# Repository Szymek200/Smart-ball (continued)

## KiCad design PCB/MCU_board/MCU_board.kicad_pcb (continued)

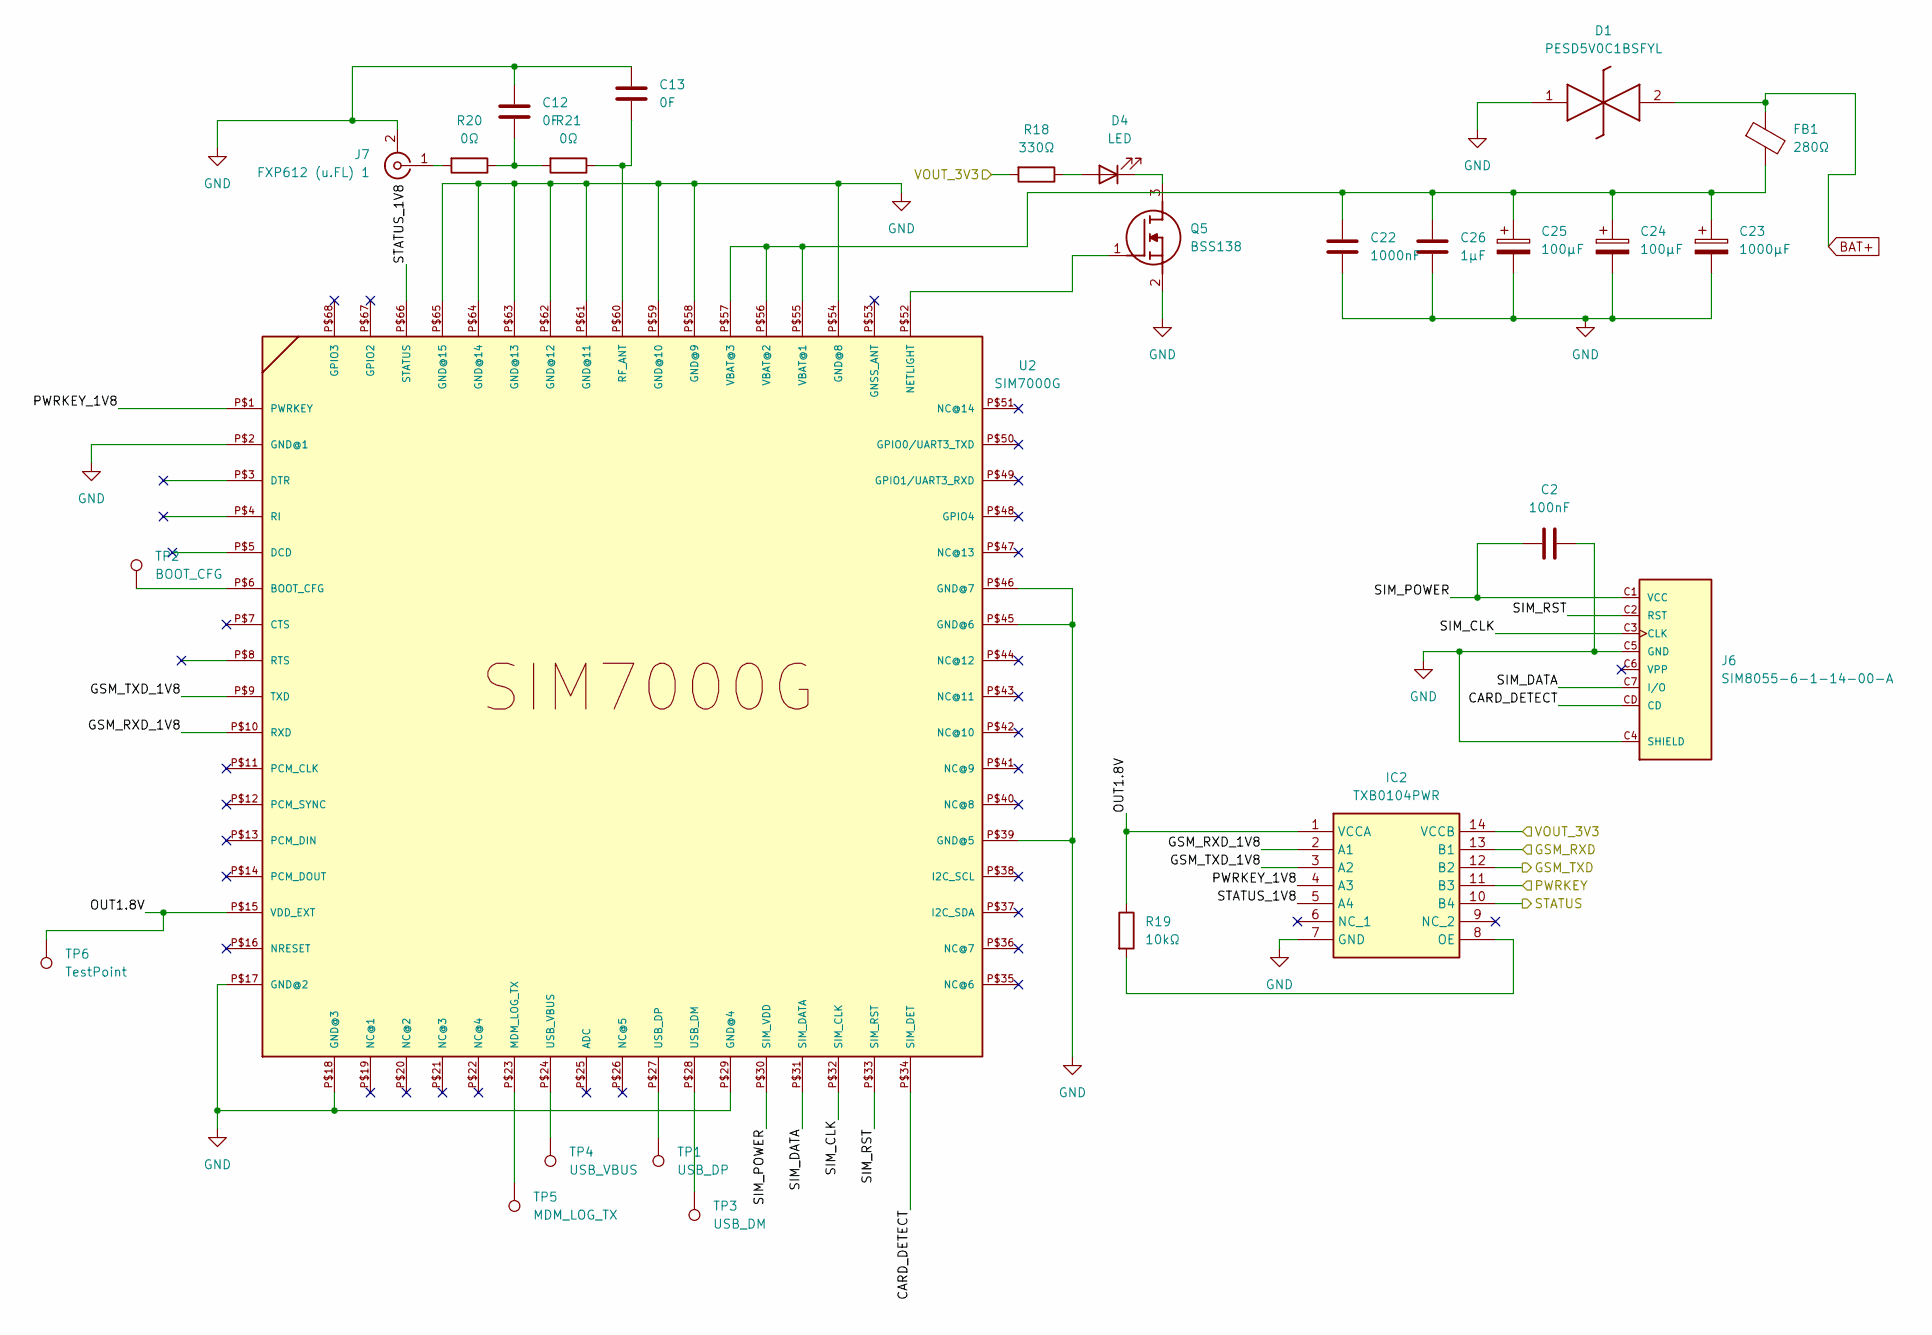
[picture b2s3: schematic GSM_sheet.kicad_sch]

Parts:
C2: 100nF; CP_Elec_6.3x5.4
C12, C13: 0F; CP_Elec_6.3x5.4
C22: 1000nF; CP_Elec_6.3x5.4
C23: 1000µF; CP_EIA-3216-18_Kemet-A
C24, C25: 100µF; CP_EIA-3216-18_Kemet-A
C26: 1µF; CP_Elec_6.3x5.4
D1: PESD5V0C1BSFYL; PMEG3005AESFYL; Mouser Part Number 771-PESD5V0C1BSFYL
D4: LED; LED_0603_1608Metric
FB1: 280Ω; L_0805_2012Metric_Pad1.05x1.20mm_HandSolder
IC2: TXB0104PWR; SOP65P640X120-14N; Mouser Part Number 595-TXB0104PWR
J6: SIM8055-6-1-14-00-A; GCT_SIM8055-6-1-14-00-A; PARTREV A1
J7: FXP612 (u.FL) 1; U.FL_Molex_MCRF_73412-0110_Vertical
Q5: BSS138; SOT95P240X120-3N; Mouser Part Number 512-BSS138
R18: 330Ω; R_0603_1608Metric
R19: 10kΩ; R_0603_1608Metric
R20, R21: 0Ω; R_0603_1608Metric
TP1: USB_DP; TestPoint_THTPad_D2.0mm_Drill1.0mm
TP2: BOOT_CFG; TestPoint_THTPad_D2.0mm_Drill1.0mm
TP3: USB_DM; TestPoint_THTPad_D2.0mm_Drill1.0mm
TP4: USB_VBUS; TestPoint_THTPad_D2.0mm_Drill1.0mm
TP5: MDM_LOG_TX; TestPoint_THTPad_D2.0mm_Drill1.0mm
TP6: TestPoint; TestPoint_THTPad_D2.0mm_Drill1.0mm
U2: SIM7000G

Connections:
/+3V3: IC2.14 (VCCB), R18.2; also elsewhere on the board
/GSM_RXT: IC2.13 (B1); also elsewhere on the board
/GSM_TXD: IC2.12 (B2); also elsewhere on the board
/PWRKEY: IC2.11 (B3); also elsewhere on the board
/STATUS: IC2.10 (B4); also elsewhere on the board
/Stationary/GSM_sheet/CARD_DETECT: J6.CD, U2.P$34 (SIM_DET)
/Stationary/GSM_sheet/GSM_RXD_1V8: IC2.2 (A1), U2.P$10 (RXD)
/Stationary/GSM_sheet/GSM_TXD_1V8: IC2.3 (A2), U2.P$9 (TXD)
/Stationary/GSM_sheet/OUT1.8V: IC2.1 (VCCA), R19.1, TP6.1 (1_1), U2.P$15 (VDD_EXT)
/Stationary/GSM_sheet/PWRKEY_1V8: IC2.4 (A3), U2.P$1 (PWRKEY)
/Stationary/GSM_sheet/SIM_CLK: J6.C3 (CLK), U2.P$32 (SIM_CLK)
/Stationary/GSM_sheet/SIM_DATA: J6.C7 (I/O), U2.P$31 (SIM_DATA)
/Stationary/GSM_sheet/SIM_POWER: C2.2, J6.C1 (VCC), U2.P$30 (SIM_VDD)
/Stationary/GSM_sheet/SIM_RST: J6.C2 (RST), U2.P$33 (SIM_RST)
/Stationary/GSM_sheet/STATUS_1V8: IC2.5 (A4), U2.P$66 (STATUS)
BAT+: D1.2 (K2), FB1.1; also elsewhere on the board
GND: C2.1, C12.1, C13.1, C22.2, C23.2, C24.2, C25.2, C26.2, D1.1 (K1), IC2.7 (GND), J6.C4 (SHIELD), J6.C5 (GND), J6.C8 (SHIELD), J7.2 (Ext), Q5.2 (S), U2.P$2 (GND@1), U2.P$17 (GND@2), U2.P$18 (GND@3), U2.P$29 (GND@4), U2.P$39 (GND@5), U2.P$45 (GND@6), U2.P$46 (GND@7), U2.P$54 (GND@8), U2.P$58 (GND@9), U2.P$59 (GND@10), U2.P$61 (GND@11), U2.P$62 (GND@12), U2.P$63 (GND@13), U2.P$64 (GND@14), U2.P$65 (GND@15); also elsewhere on the board
unnamed: C12.2, R20.1, R21.2
unnamed: D4.2 (A), R18.1
unnamed: D4.1 (K), Q5.3 (D)
unnamed: IC2.8 (OE), R19.2
unnamed: J7.1 (In), R20.2
unnamed: Q5.1 (G), U2.P$52 (NETLIGHT)
unnamed: TP2.1 (1_1), U2.P$6 (BOOT_CFG)
unnamed: TP5.1 (1_1), U2.P$23 (MDM_LOG_TX)
unnamed: C13.2, R21.1, U2.P$60 (RF_ANT)
unnamed: TP3.1 (1_1), U2.P$28 (USB_DM)
unnamed: TP1.1 (1_1), U2.P$27 (USB_DP)
unnamed: TP4.1 (1_1), U2.P$24 (USB_VBUS)
unnamed: C22.1, C23.1, C24.1, C25.1, C26.1, FB1.2, U2.P$55 (VBAT@1), U2.P$56 (VBAT@2), U2.P$57 (VBAT@3)

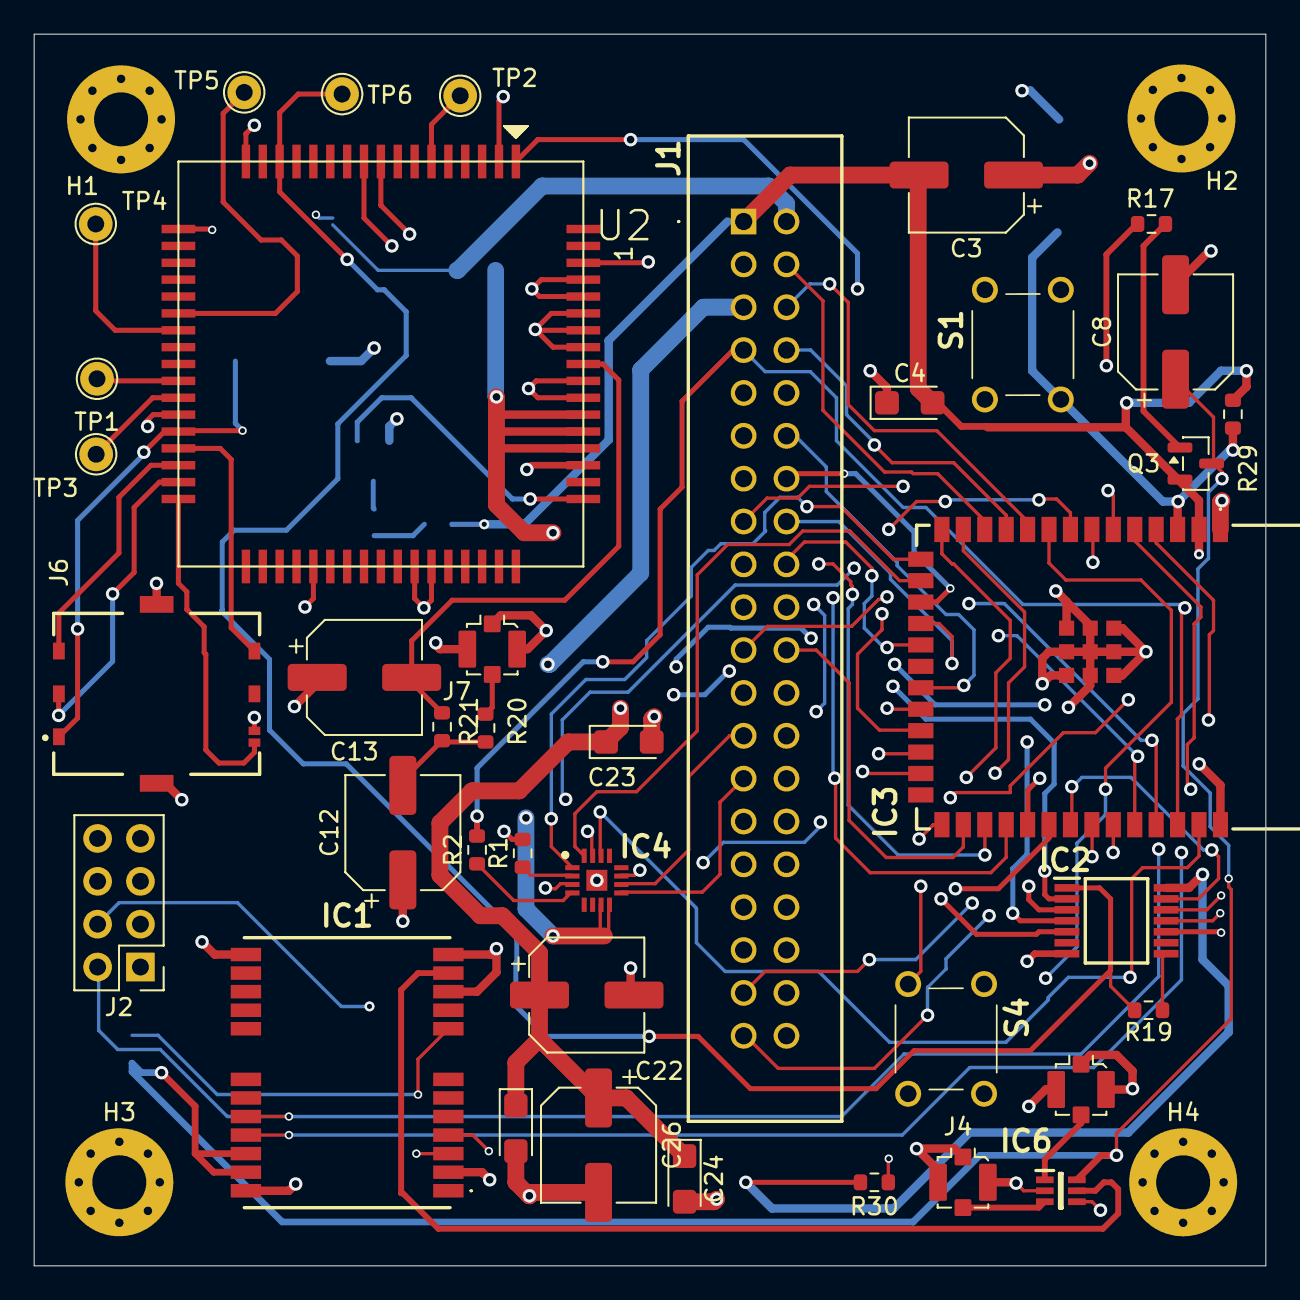
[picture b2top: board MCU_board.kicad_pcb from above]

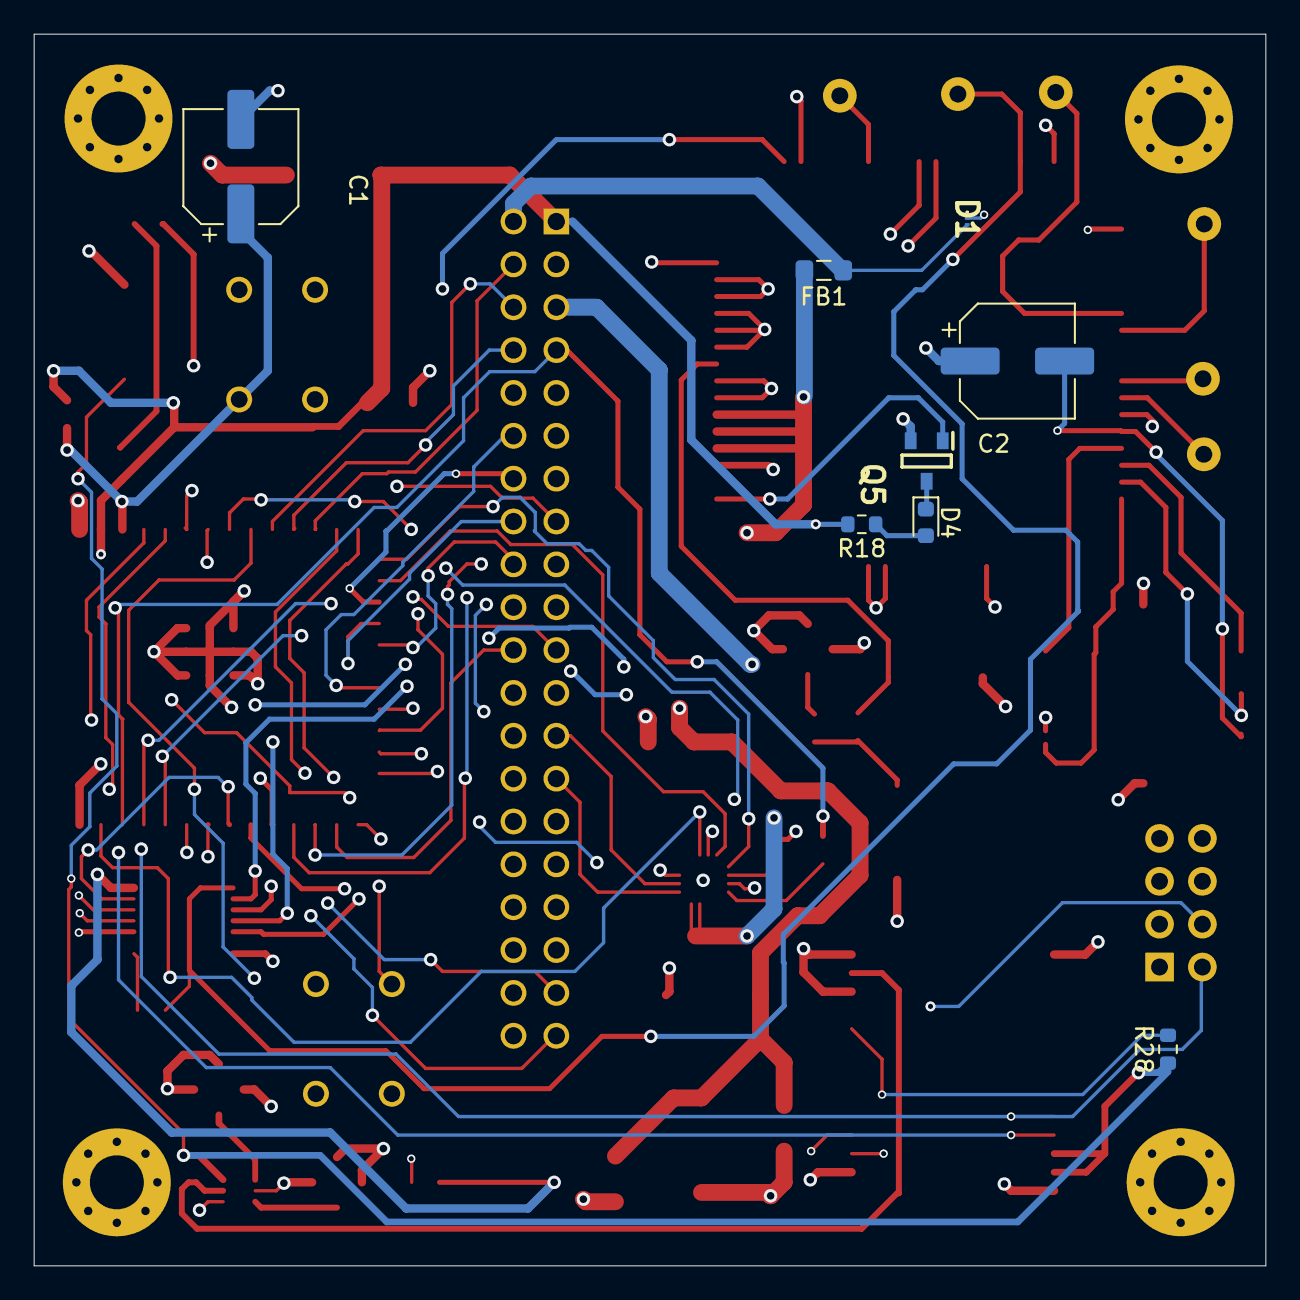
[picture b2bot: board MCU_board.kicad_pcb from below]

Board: 4 copper layers, 73.0 x 73.0 mm, 51 parts (8 on the bottom side), 72 nets.

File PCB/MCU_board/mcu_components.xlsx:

Designator | Footprint | Quantity | Value | LCSC Part #
C1, C26 | C_Disc_D5.0mm_W2.5mm_P2.50mm | 2 | 1μF
C12, C13 | C_Disc_D5.0mm_W2.5mm_P2.50mm | 2 | 0F
C2, C3 | C_Disc_D5.0mm_W2.5mm_P2.50mm | 2 | 100nF
C22 | C_Disc_D5.0mm_W2.5mm_P2.50mm | 1 | 1000nF
C23 | CP_Radial_Tantal_D5.0mm_P2.50mm | 1 | 1000µF
C24, C25 | CP_Radial_Tantal_D5.0mm_P2.50mm | 2 | 100µF
C4 | CP_Radial_Tantal_D5.0mm_P2.50mm | 1 | 1μF
C8 | C_Disc_D5.0mm_W2.5mm_P2.50mm | 1 | 100 nF
D1 | PMEG3005AESFYL | 1 | PESD5V0C1BSFYL
D4 | D_DO-41_SOD81_P7.62mm_Horizontal | 1 | LED
FB1 | 805 | 1 | 280Ω
IC1 | NEOF10N00B | 1 | NEO-F10N-00B
IC2 | SOP65P640X120-14N | 1 | TXB0104PWR
IC3 | ESP32S3WROOM1N4R8 | 1 | ESP32-S3-WROOM-1-N4R8
IC6 | SOT65P210X110-6N | 1 | 4259-63
IC8 | QFN50P300X300X80-17N | 1 | MAX98357AETE+T
J1 | DS101340SSIB1B0 | 1 | DS1013-40SSIB1-B-0
J4 | U.FL_Molex_MCRF_73412-0110_Vertical | 1 | FXP612 (u.FL) 2
J5, J7 | U.FL_Molex_MCRF_73412-0110_Vertical | 2 | FXP612 (u.FL) 1
J6 | GCT_SIM8055-6-1-14-00-A | 1 | SIM8055-6-1-14-00-A
Q3 | SOT95P237X112-3N | 1 | Si2323DDS-T1-GE3
Q5 | SOT95P240X120-3N | 1 | BSS138
R16, R26 | R_Axial_DIN0207_L6.3mm_D2.5mm_P7.62mm_Horizontal | 2 | 100kΩ
R17, R19, R28, R29, R30 | R_Axial_DIN0207_L6.3mm_D2.5mm_P7.62mm_Horizontal | 5 | 10kΩ
R18 | R_Axial_DIN0207_L6.3mm_D2.5mm_P7.62mm_Horizontal | 1 | 330Ω
R20, R21 | R_Axial_DIN0207_L6.3mm_D2.5mm_P7.62mm_Horizontal | 2 | 0Ω
S1, S4 | 18259106 | 2 | 1825910-6
TP1 | TestPoint_THTPad_D2.0mm_Drill1.0mm | 1 | USB_DP
TP2 | TestPoint_THTPad_D2.0mm_Drill1.0mm | 1 | BOOT_CFG
TP3 | TestPoint_THTPad_D2.0mm_Drill1.0mm | 1 | USB_DM
TP4 | TestPoint_THTPad_D2.0mm_Drill1.0mm | 1 | USB_VBUS
TP5 | TestPoint_THTPad_D2.0mm_Drill1.0mm | 1 | MDM_LOG_TX
TP6 | TestPoint_THTPad_D2.0mm_Drill1.0mm | 1 | TestPoint
U2 | SIM7000G | 1 | SIM7000G

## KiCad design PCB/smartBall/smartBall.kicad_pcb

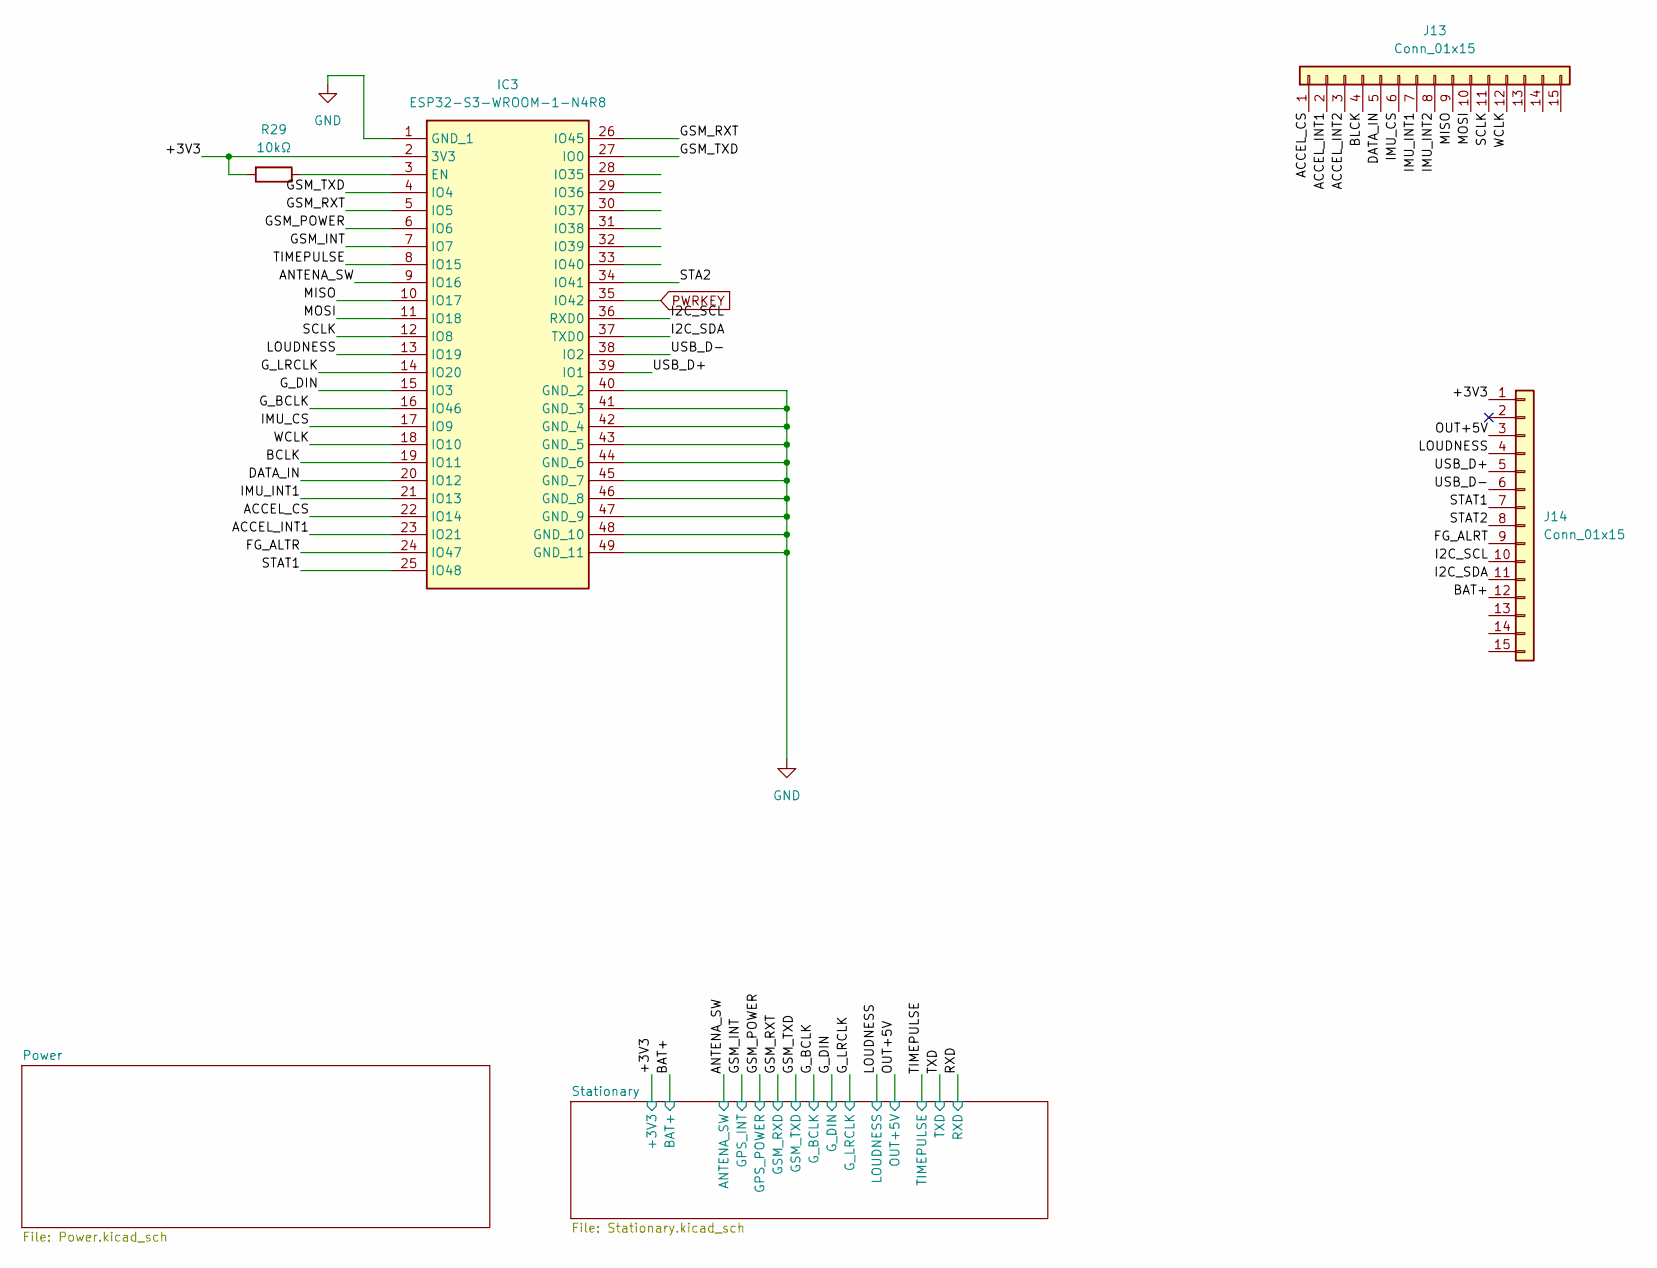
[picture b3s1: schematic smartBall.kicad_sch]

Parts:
IC3: ESP32-S3-WROOM-1-N4R8; ESP32S3WROOM1N4R8; Mouser Part Number 356-ESP32S3WROM1N4R8
J13, J14: Conn_01x15; PinHeader_1x15_P2.54mm_Vertical
R29: 10kΩ; R_Axial_DIN0207_L6.3mm_D2.5mm_P7.62mm_Horizontal

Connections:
/+3V3: IC3.2 (3V3), J14.1, R29.2; also elsewhere on the board
/ACCEL_CS: IC3.22 (IO14), J13.1
/ACCEL_INT1: IC3.23 (IO21), J13.2
/ACCEL_INT2: IC3.28 (IO35), J13.3
/ANTENA_SW: IC3.9 (IO16); also elsewhere on the board
/BAT+: J14.12
/DATA_IN: IC3.20 (IO12), J13.5
/GSM_INT: IC3.7 (IO7); also elsewhere on the board
/GSM_POWER: IC3.6 (IO6); also elsewhere on the board
/G_BCLK: IC3.16 (IO46); also elsewhere on the board
/G_DIN: IC3.15 (IO3); also elsewhere on the board
/G_LRCLK: IC3.14 (IO20); also elsewhere on the board
/I2C_SCL: IC3.36 (RXD0), J14.10
/I2C_SDA: IC3.37 (TXD0), J14.11
/IMU_CS: IC3.17 (IO9), J13.6
/IMU_INT1: IC3.21 (IO13), J13.7
/IMU_INT2: IC3.29 (IO36), J13.8
/LOUDNESS: IC3.13 (IO19), J14.4; also elsewhere on the board
/MISO: IC3.10 (IO17), J13.9
/MOSI: IC3.11 (IO18), J13.10
/OUT+5V: J14.3; also elsewhere on the board
/PWRKEY: IC3.31 (IO38); also elsewhere on the board
/SCLK: IC3.12 (IO8), J13.11
/STAT1: IC3.25 (IO48), J14.7
/STATUS: IC3.32 (IO39); also elsewhere on the board
/TIMEPULSE: IC3.8 (IO15); also elsewhere on the board
/TS/CTRL: IC3.30 (IO37), J14.2
/USB_D+: IC3.39 (IO1), J14.5
/USB_D-: IC3.38 (IO2), J14.6
/WCLK: IC3.18 (IO10), J13.12
GND: IC3.1 (GND_1), IC3.40 (GND_2), IC3.41 (GND_3), IC3.42 (GND_4), IC3.43 (GND_5), IC3.44 (GND_6), IC3.45 (GND_7), IC3.46 (GND_8), IC3.47 (GND_9), IC3.48 (GND_10), IC3.49 (GND_11); also elsewhere on the board
unnamed: IC3.3 (EN), R29.1

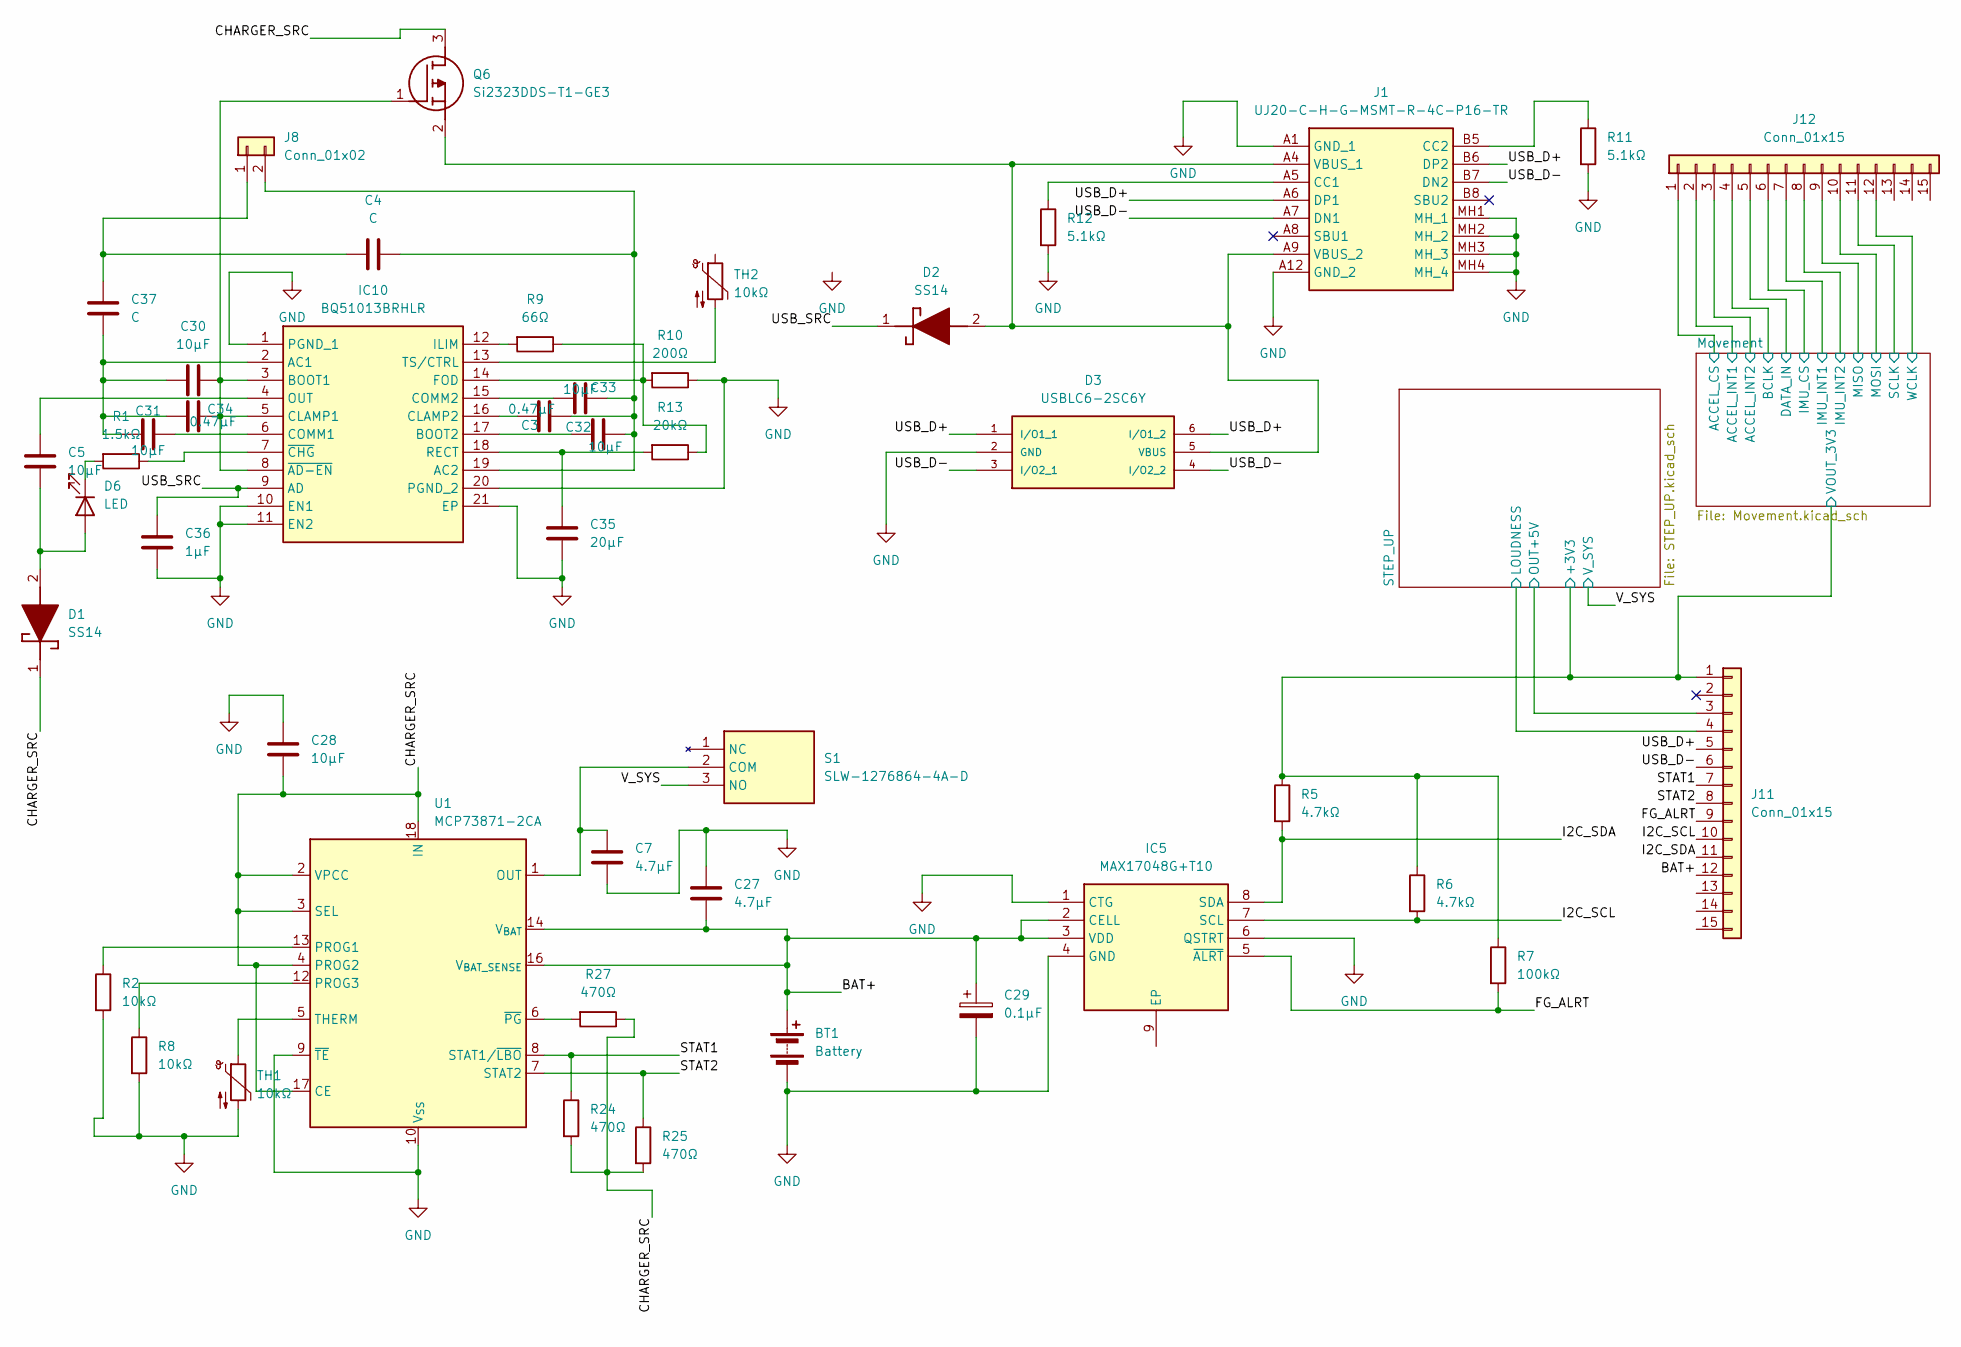
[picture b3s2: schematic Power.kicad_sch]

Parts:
BT1: Battery; SolderWire-0.75sqmm_1x02_P4.8mm_D1.25mm_OD2.3mm
C3, C34: 0.47µF; CP_Radial_Tantal_D5.0mm_P2.50mm
C4, C37: C; CP_Radial_Tantal_D5.0mm_P2.50mm
C5, C28, C30, C31, C32, C33: 10µF; CP_Radial_Tantal_D5.0mm_P2.50mm
C7, C27: 4.7µF; CP_Radial_Tantal_D5.0mm_P2.50mm
C29: 0.1µF; CP_Radial_Tantal_D5.0mm_P2.50mm
C35: 20µF; CP_Radial_Tantal_D5.0mm_P2.50mm
C36: 1µF; CP_Radial_Tantal_D5.0mm_P2.50mm
D1, D2: SS14; DIOM5227X270N; Mouser Part Number 512-SS14
D3: USBLC6-2SC6Y; SOT95P280X145-6N; MOUSER_PART_NUMBER 511-USBLC6-2SC6Y
D6: LED; D_DO-41_SOD81_P7.62mm_Horizontal
IC5: MAX17048G+T10; SON50P200X200X80-9N-D; Mouser Part Number 700-MAX17048G+T10
IC10: BQ51013BRHLR; BQ51050BRHLR; Mouser Part Number 595-BQ51013BRHLR
J1: UJ20-C-H-G-MSMT-R-4C-P16-TR; UJ20CHGMSMTR4CP16TR; Manufacturer_Part_Number UJ20-C-H-G-MSMT-R-4C-P16-TR
J8: Conn_01x02; PinHeader_1x02_P2.54mm_Vertical
J11, J12: Conn_01x15; PinHeader_1x15_P2.54mm_Vertical
Q6: Si2323DDS-T1-GE3; SOT95P237X112-3N; Mouser Part Number 78-SI2323DDS-T1-GE3
R1: 1.5kΩ; R_Axial_DIN0207_L6.3mm_D2.5mm_P7.62mm_Horizontal
R2, R8: 10kΩ; R_Axial_DIN0207_L6.3mm_D2.5mm_P7.62mm_Horizontal
R5, R6: 4.7kΩ; R_Axial_DIN0207_L6.3mm_D2.5mm_P7.62mm_Horizontal
R7: 100kΩ; R_Axial_DIN0207_L6.3mm_D2.5mm_P7.62mm_Horizontal
R9: 66Ω; R_Axial_DIN0207_L6.3mm_D2.5mm_P7.62mm_Horizontal
R10: 200Ω; R_Axial_DIN0207_L6.3mm_D2.5mm_P7.62mm_Horizontal
R11, R12: 5.1kΩ; R_Axial_DIN0207_L6.3mm_D2.5mm_P7.62mm_Horizontal
R13: 20kΩ; R_Axial_DIN0207_L6.3mm_D2.5mm_P7.62mm_Horizontal
R24, R25, R27: 470Ω; R_Axial_DIN0207_L6.3mm_D2.5mm_P7.62mm_Horizontal
S1: SLW-1276864-4A-D; SLW12768644AD; Mouser Part Number 179-SLW-1276864-4A-D
TH1, TH2: 10kΩ; R_Axial_DIN0207_L6.3mm_D2.5mm_P7.62mm_Horizontal
U1: MCP73871-2CA; QFN-20-1EP_4x4mm_P0.5mm_EP2.5x2.5mm

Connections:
/Power/BAT+: BT1.1 (+), C27.2, C29.1, IC5.2 (CELL), IC5.3 (VDD), J11.12, U1.14 (V_{BAT}), U1.15 (V_{BAT}), U1.16 (V_{BAT_SENSE})
/Power/CHARGER_SRC: C28.2, D1.1 (K), Q6.3 (D), R24.2, R25.2, R27.1, U1.2 (VPCC), U1.3 (SEL), U1.4 (PROG2), U1.17 (CE), U1.18 (IN), U1.19 (IN)
/Power/FG_ALRT: IC5.5 (~ALRT), J11.9, R7.2
/Power/I2C_SCL: IC5.7 (SCL), J11.10, R6.2
/Power/I2C_SDA: IC5.8 (SDA), J11.11, R5.2
/Power/Movement/ACCEL_CS: J12.1; also elsewhere on the board
/Power/Movement/ACCEL_INT1: J12.2; also elsewhere on the board
/Power/Movement/ACCEL_INT2: J12.3; also elsewhere on the board
/Power/Movement/BCLK: J12.4; also elsewhere on the board
/Power/Movement/DATA_IN: J12.5; also elsewhere on the board
/Power/Movement/IMU_CS: J12.6; also elsewhere on the board
/Power/Movement/IMU_INT1: J12.7; also elsewhere on the board
/Power/Movement/IMU_INT2: J12.8; also elsewhere on the board
/Power/Movement/MISO: J12.9; also elsewhere on the board
/Power/Movement/MOSI: J12.10; also elsewhere on the board
/Power/Movement/SCLK: J12.11; also elsewhere on the board
/Power/Movement/VOUT_3V3: J11.1, R5.1, R6.1, R7.1; also elsewhere on the board
/Power/Movement/WCLK: J12.12; also elsewhere on the board
/Power/STAT1: J11.7, R24.1, U1.8 (STAT1/~LBO)
/Power/STAT2: J11.8, R25.1, U1.7 (STAT2)
/Power/STEP_UP/LOUDNESS: J11.4; also elsewhere on the board
/Power/STEP_UP/OUT+5V: J11.3; also elsewhere on the board
/Power/USB_D+: D3.1 (I/O1_1), D3.6 (I/O1_2), J1.A6 (DP1), J1.B6 (DP2), J11.5
/Power/USB_D-: D3.3 (I/O2_1), D3.4 (I/O2_2), J1.A7 (DN1), J1.B7 (DN2), J11.6
/Power/USB_SRC: C36.1, D2.1 (K), IC10.9 (AD)
/Power/V_SYS: S1.3 (NO); also elsewhere on the board
GND: BT1.2 (-), C7.2, C27.1, C28.1, C29.2, C35.2, C36.2, D3.2 (GND), IC5.1 (CTG), IC5.4 (GND), IC5.6 (QSTRT), IC5.9 (EP), IC10.1 (PGND_1), IC10.10 (EN1), IC10.11 (EN2), IC10.20 (PGND_2), IC10.21 (EP), J1.A1 (GND_1), J1.A12 (GND_2), J1.MH1 (MH_1), J1.MH2 (MH_2), J1.MH3 (MH_3), J1.MH4 (MH_4), R2.2, R8.2, R10.1, R11.2, R12.2, TH1.2, TH2.1, U1.9 (~TE), U1.10 (V_{SS}), U1.11 (V_{SS}), U1.21 (V_{SS}); also elsewhere on the board
unnamed: C5.2, D1.2 (A), D6.2 (A)
unnamed: D2.2 (A), D3.5 (VBUS), J1.A4 (VBUS_1), J1.A9 (VBUS_2), Q6.2 (S)
unnamed: D6.1 (K), R1.2
unnamed: C30.2, C31.2, C34.2, C37.2, IC10.2 (AC1)
unnamed: C3.1, C4.1, C32.1, C33.1, IC10.19 (AC2), J8.2
unnamed: C30.1, C34.1, IC10.3 (BOOT1), IC10.5 (CLAMP1), IC10.8 (~AD-EN), Q6.1 (G)
unnamed: C32.2, IC10.17 (BOOT2)
unnamed: C3.2, IC10.16 (CLAMP2)
unnamed: C31.1, IC10.6 (COMM1)
unnamed: C33.2, IC10.15 (COMM2)
unnamed: IC10.14 (FOD), R9.1, R10.2, R13.1
unnamed: IC10.12 (ILIM), R9.2
unnamed: C5.1, IC10.4 (OUT)
unnamed: C35.1, IC10.18 (RECT), R13.2
unnamed: IC10.7 (~CHG), R1.1
unnamed: J1.A5 (CC1), R12.1
unnamed: J1.B5 (CC2), R11.1
unnamed: C4.2, C37.1, J8.1
unnamed: C7.1, S1.2 (COM), U1.1 (OUT), U1.20 (OUT)
unnamed: R2.1, U1.13 (PROG1)
unnamed: R8.1, U1.12 (PROG3)
unnamed: TH1.1, U1.5 (THERM)
unnamed: R27.2, U1.6 (~PG)

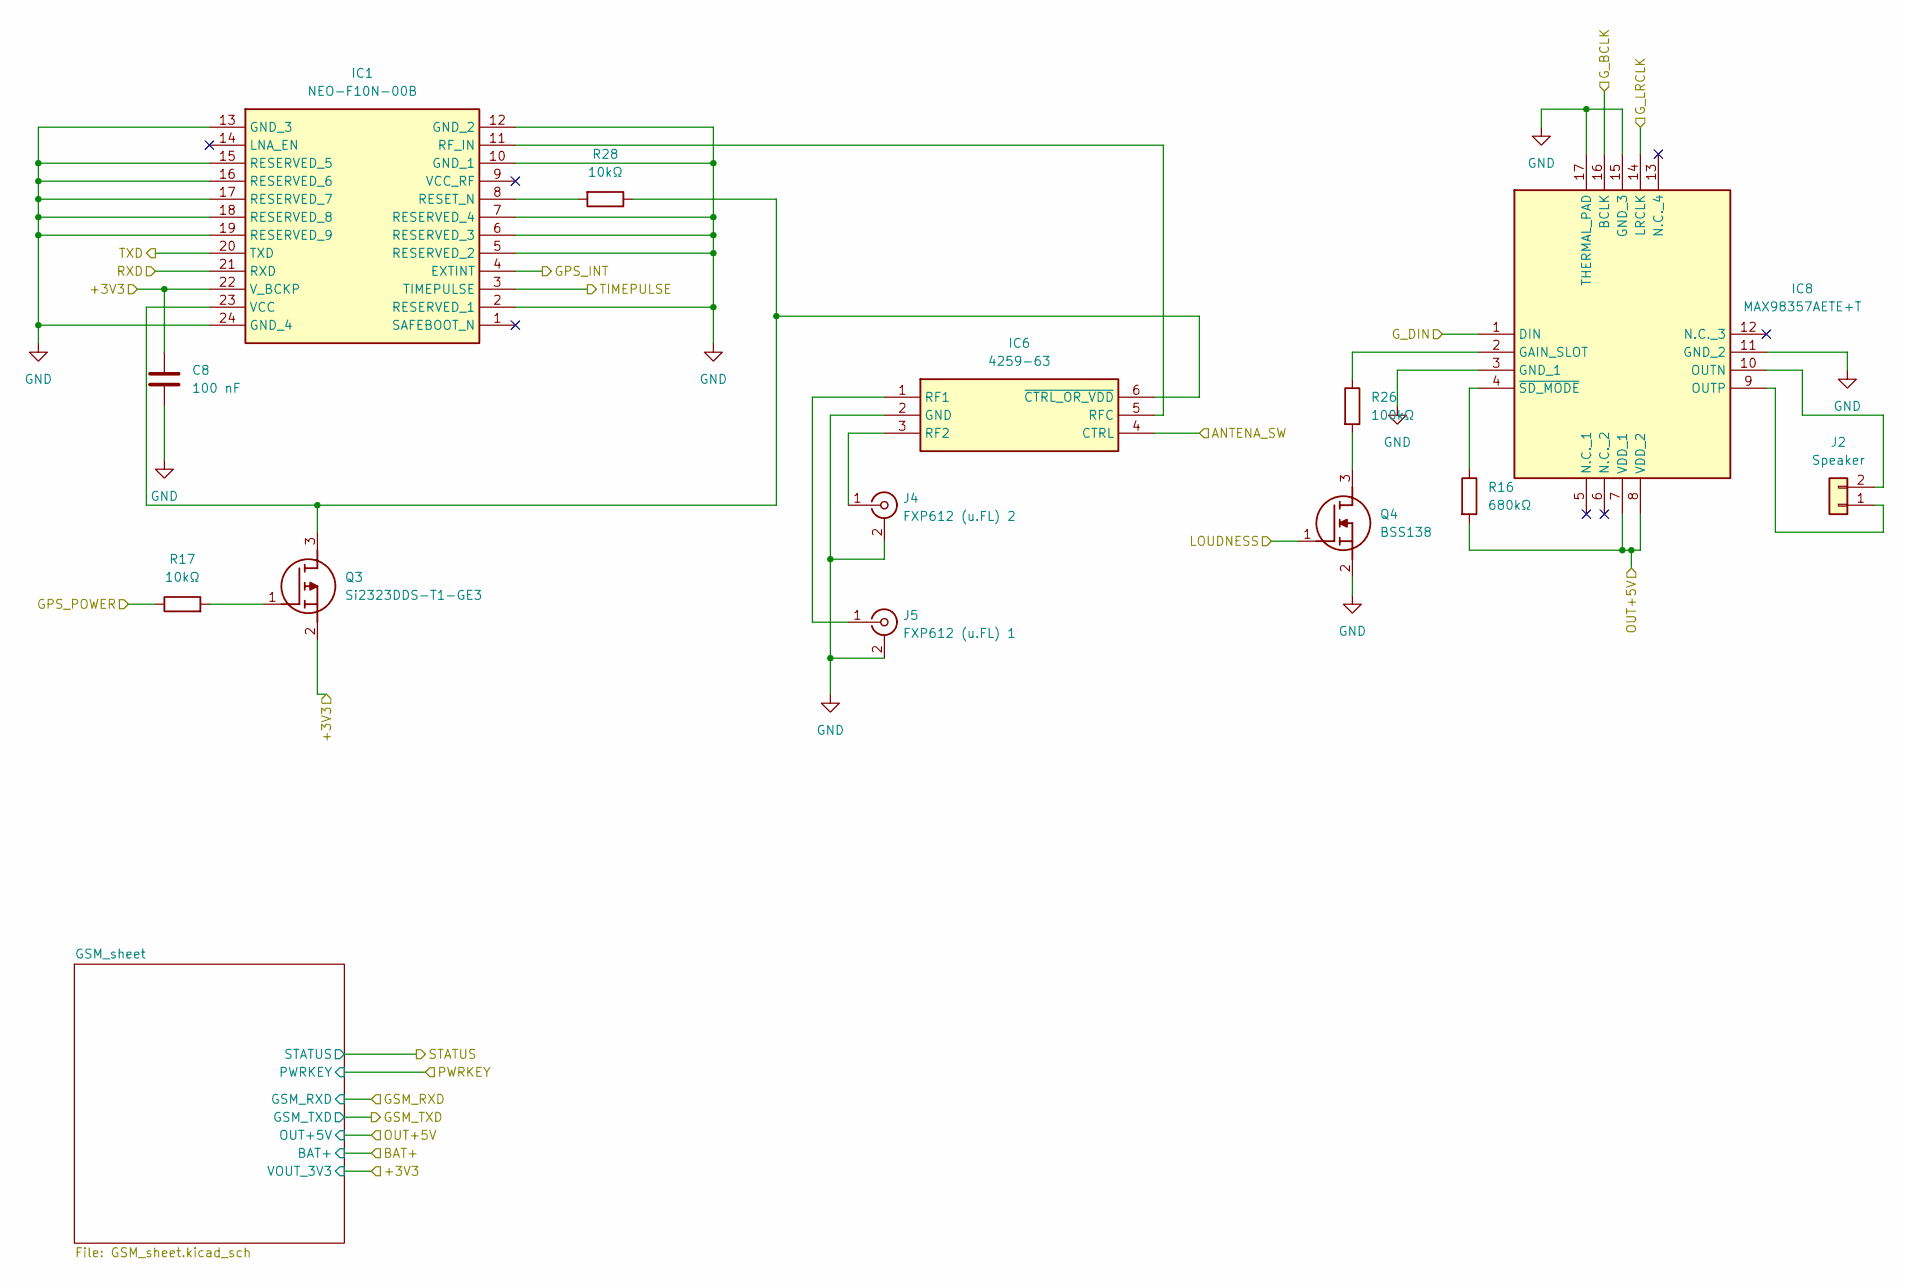
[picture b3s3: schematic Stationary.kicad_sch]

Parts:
C8: 100 nF; C_Disc_D5.0mm_W2.5mm_P2.50mm
IC1: NEO-F10N-00B; NEOF10N00B; Mouser Part Number 377-NEO-F10N-00B
IC6: 4259-63; SOT65P210X110-6N; Mouser Part Number 81-4259-63
IC8: MAX98357AETE+T; QFN50P300X300X80-17N; Mouser Part Number 700-MAX98357AETE+T
J2: Speaker; JST_PH_B2B-PH-K_1x02_P2.00mm_Vertical
J4: FXP612 (u.FL) 2; U.FL_Molex_MCRF_73412-0110_Vertical
J5: FXP612 (u.FL) 1; U.FL_Molex_MCRF_73412-0110_Vertical
Q3: Si2323DDS-T1-GE3; SOT95P237X112-3N; Mouser Part Number 78-SI2323DDS-T1-GE3
Q4: BSS138; SOT95P240X120-3N; Mouser Part Number 512-BSS138
R16: 680kΩ; R_Axial_DIN0207_L6.3mm_D2.5mm_P7.62mm_Horizontal
R17, R28: 10kΩ; R_Axial_DIN0207_L6.3mm_D2.5mm_P7.62mm_Horizontal
R26: 100kΩ; R_Axial_DIN0207_L6.3mm_D2.5mm_P7.62mm_Horizontal

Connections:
/+3V3: C8.1, IC1.22 (V_BCKP), Q3.2 (S); also elsewhere on the board
/ANTENA_SW: IC6.4 (CTRL); also elsewhere on the board
/GSM_INT: IC1.4 (EXTINT); also elsewhere on the board
/GSM_POWER: R17.1; also elsewhere on the board
/G_BCLK: IC8.16 (BCLK); also elsewhere on the board
/G_DIN: IC8.1 (DIN); also elsewhere on the board
/G_LRCLK: IC8.14 (LRCLK); also elsewhere on the board
/LOUDNESS: Q4.1 (G); also elsewhere on the board
/OUT+5V: IC8.7 (VDD_1), IC8.8 (VDD_2), R16.2; also elsewhere on the board
/TIMEPULSE: IC1.3 (TIMEPULSE); also elsewhere on the board
GND: C8.2, IC1.2 (RESERVED_1), IC1.5 (RESERVED_2), IC1.6 (RESERVED_3), IC1.7 (RESERVED_4), IC1.10 (GND_1), IC1.12 (GND_2), IC1.13 (GND_3), IC1.15 (RESERVED_5), IC1.16 (RESERVED_6), IC1.17 (RESERVED_7), IC1.18 (RESERVED_8), IC1.19 (RESERVED_9), IC1.24 (GND_4), IC6.2 (GND), IC8.3 (GND_1), IC8.11 (GND_2), IC8.15 (GND_3), IC8.17 (THERMAL_PAD), J4.2 (Ext), J5.2 (Ext), Q4.2 (S); also elsewhere on the board
unnamed: IC1.8 (RESET_N), R28.2
unnamed: IC1.11 (RF_IN), IC6.5 (RFC)
unnamed: IC1.23 (VCC), IC6.6 (~CTRL_OR_VDD), Q3.3 (D), R28.1
unnamed: IC6.1 (RF1), J5.1 (In)
unnamed: IC6.3 (RF2), J4.1 (In)
unnamed: IC8.2 (GAIN_SLOT), R26.1
unnamed: IC8.10 (OUTN), J2.2
unnamed: IC8.9 (OUTP), J2.1
unnamed: IC8.4 (~SD_MODE), R16.1
unnamed: Q3.1 (G), R17.2
unnamed: Q4.3 (D), R26.2
